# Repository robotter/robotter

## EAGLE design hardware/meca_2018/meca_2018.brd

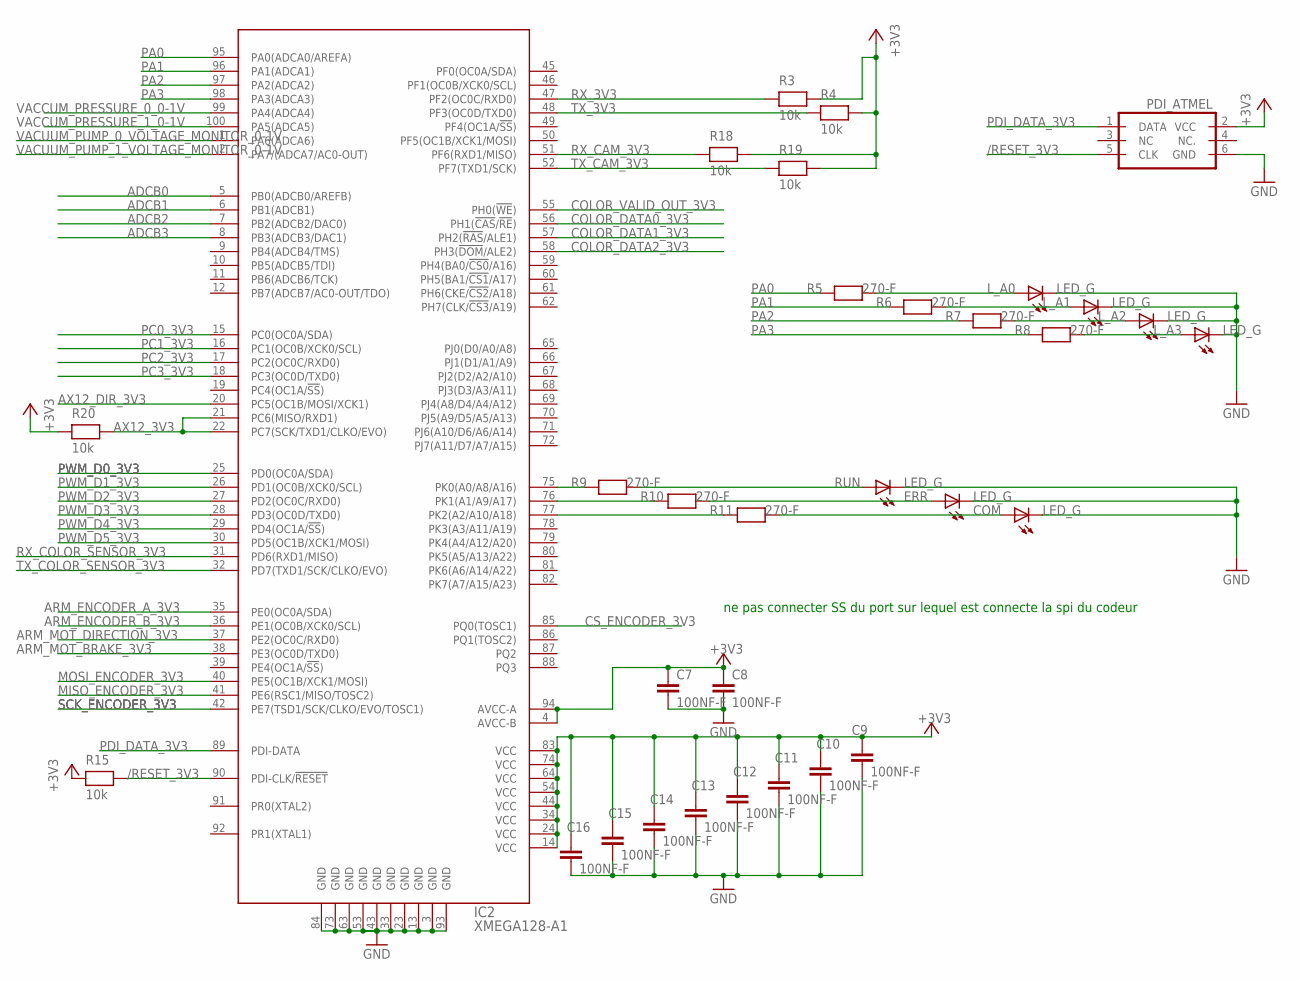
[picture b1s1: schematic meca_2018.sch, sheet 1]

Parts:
C7, C8, C9, C10, C11, C12, C13, C14, C15, C16: 100NF-F; C0603
COM: LED_G; CHIP-LED0805
ERR: LED_G; CHIP-LED0805
IC2: XMEGA128-A1; TQFP100
L_A0, L_A1, L_A2, L_A3: LED_G; CHIP-LED0805
PDI_ATMEL: PDI_ATMEL; ML6
R3, R4, R15, R18, R19, R20: 10k; R0603
R5, R6, R7, R8, R9, R10, R11: 270-F; R0603
RUN: LED_G; CHIP-LED0805

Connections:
+3V3: C7.1, C8.1, C9.1, C10.1, C11.1, C12.1, C13.1, C14.1, C15.1, C16.1, IC2.4 (AVCC-B), IC2.14 (VCC), IC2.24 (VCC), IC2.34 (VCC), IC2.44 (VCC), IC2.54 (VCC), IC2.64 (VCC), IC2.74 (VCC), IC2.83 (VCC), IC2.94 (AVCC-A), PDI_ATMEL.2 (VCC), R3.2, R4.2, R15.1, R18.2, R19.2, R20.1; also elsewhere on the board
/RESET_3V3: IC2.90 (PDI-CLK/!RESET), PDI_ATMEL.5 (CLK), R15.2
ADCB0: IC2.5 (PB0(ADCB0/AREFB))
ADCB1: IC2.6 (PB1(ADCB1))
ADCB2: IC2.7 (PB2(ADCB2/DAC0))
ADCB3: IC2.8 (PB3(ADCB3/DAC1))
ARM_ENCODER_A_3V3: IC2.35 (PE0(OC0A/SDA))
ARM_ENCODER_B_3V3: IC2.36 (PE1(OC0B/XCK0/SCL))
ARM_MOT_BRAKE_3V3: IC2.38 (PE3(OC0D/TXD0))
ARM_MOT_DIRECTION_3V3: IC2.37 (PE2(OC0C/RXD0))
AX12_3V3: IC2.21 (PC6(MISO/RXD1)), IC2.22 (PC7(SCK/TXD1/CLKO/EVO)), R20.2; also elsewhere on the board
AX12_DIR_3V3: IC2.20 (PC5(OC1B/MOSI/XCK1)); also elsewhere on the board
COLOR_DATA0_3V3: IC2.56 (PH1(!CAS!/!RE!))
COLOR_DATA1_3V3: IC2.57 (PH2(!RAS!/ALE1))
COLOR_DATA2_3V3: IC2.58 (PH3(!DOM!/ALE2))
COLOR_VALID_OUT_3V3: IC2.55 (PH0(!WE!))
CS_ENCODER_3V3: IC2.85 (PQ0(TOSC1))
GND: C7.2, C8.2, C9.2, C10.2, C11.2, C12.2, C13.2, C14.2, C15.2, C16.2, COM.C, ERR.C, IC2.3 (GND), IC2.13 (GND), IC2.23 (GND), IC2.33 (GND), IC2.43 (GND), IC2.53 (GND), IC2.63 (GND), IC2.73 (GND), IC2.84 (GND), IC2.93 (GND), L_A0.C, L_A1.C, L_A2.C, L_A3.C, PDI_ATMEL.6 (GND), RUN.C; also elsewhere on the board
MISO_ENCODER_3V3: IC2.41 (PE6(RSC1/MISO/TOSC2)); also elsewhere on the board
MOSI_ENCODER_3V3: IC2.40 (PE5(OC1B/XCK1/MOSI))
unnamed: R9.2, RUN.A
unnamed: ERR.A, R10.2
unnamed: COM.A, R11.2
unnamed: IC2.75 (PK0(A0/A8/A16)), R9.1
unnamed: IC2.76 (PK1(A1/A9/A17)), R10.1
unnamed: IC2.77 (PK2(A2/A10/A18)), R11.1
unnamed: L_A0.A, R5.2
unnamed: L_A1.A, R6.2
unnamed: L_A2.A, R7.2
unnamed: L_A3.A, R8.2
PA0: IC2.95 (PA0(ADCA0/AREFA)), R5.1
PA1: IC2.96 (PA1(ADCA1)), R6.1
PA2: IC2.97 (PA2(ADCA2)), R7.1
PA3: IC2.98 (PA3(ADCA3)), R8.1
PC0_3V3: IC2.15 (PC0(OC0A/SDA))
PC1_3V3: IC2.16 (PC1(OC0B/XCK0/SCL))
PC2_3V3: IC2.17 (PC2(OC0C/RXD0))
PC3_3V3: IC2.18 (PC3(OC0D/TXD0))
PDI_DATA_3V3: IC2.89 (PDI-DATA), PDI_ATMEL.1 (DATA)
PWM_D0_3V3: IC2.25 (PD0(OC0A/SDA)); also elsewhere on the board
PWM_D1_3V3: IC2.26 (PD1(OC0B/XCK0/SCL)); also elsewhere on the board
PWM_D2_3V3: IC2.27 (PD2(OC0C/RXD0)); also elsewhere on the board
PWM_D3_3V3: IC2.28 (PD3(OC0D/TXD0)); also elsewhere on the board
PWM_D4_3V3: IC2.29 (PD4(OC1A/!SS!)); also elsewhere on the board
PWM_D5_3V3: IC2.30 (PD5(OC1B/XCK1/MOSI)); also elsewhere on the board
RX_3V3: IC2.47 (PF2(OC0C/RXD0)), R3.1; also elsewhere on the board
RX_CAM_3V3: IC2.51 (PF6(RXD1/MISO)), R18.1; also elsewhere on the board
RX_COLOR_SENSOR_3V3: IC2.31 (PD6(RXD1/MISO))
SCK_ENCODER_3V3: IC2.42 (PE7(TSD1/SCK/CLKO/EVO/TOSC1))
TX_3V3: IC2.48 (PF3(OC0D/TXD0)), R4.1; also elsewhere on the board
TX_CAM_3V3: IC2.52 (PF7(TXD1/SCK)), R19.1; also elsewhere on the board
TX_COLOR_SENSOR_3V3: IC2.32 (PD7(TXD1/SCK/CLKO/EVO))
VACCUM_PRESSURE_0_0-1V: IC2.99 (PA4(ADCA4))
VACCUM_PRESSURE_1_0-1V: IC2.100 (PA5(ADCA5))
VACUUM_PUMP_0_VOLTAGE_MONITOR_0-1V: IC2.1 (PA6(ADCA6))
VACUUM_PUMP_1_VOLTAGE_MONITOR_0-1V: IC2.2 (PA7/(ADCA7/AC0-OUT))

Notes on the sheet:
ne pas connecter SS du port sur lequel est connecte la spi du codeur

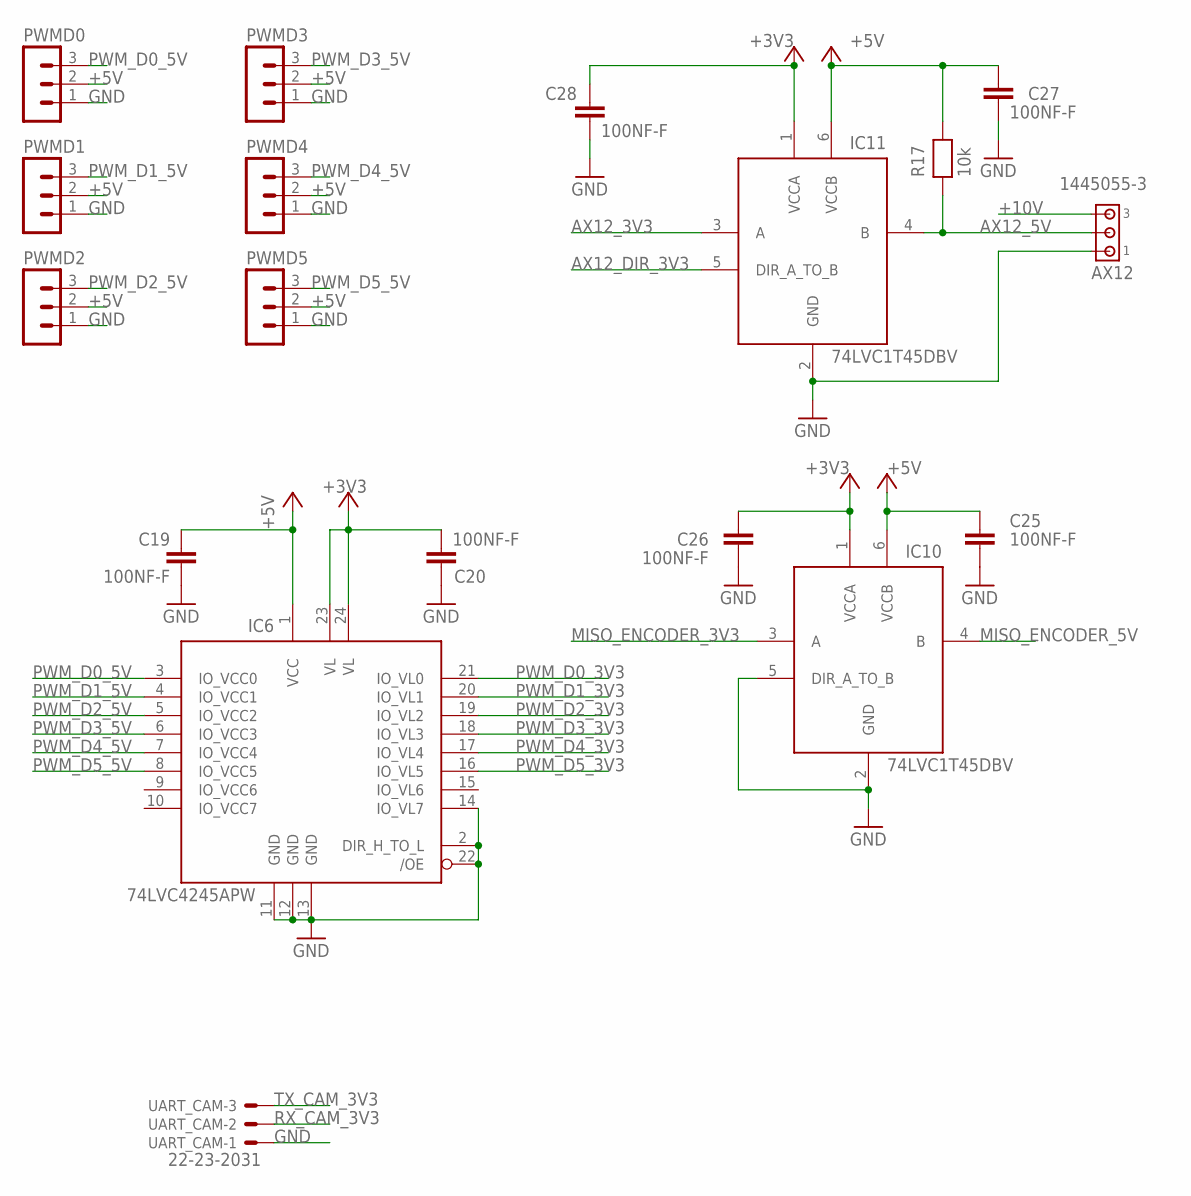
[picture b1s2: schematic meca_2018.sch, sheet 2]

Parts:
AX12: 1445055-3
C19, C20, C25, C26, C27, C28: 100NF-F; C0603
IC6: 74LVC4245APW; TSSOP24
IC10, IC11: 74LVC1T45DBV; SOT23-6
PWMD0, PWMD1, PWMD2, PWMD3, PWMD4, PWMD5: MA03-1
R17: 10k; R0603
UART_CAM: 22-23-2031

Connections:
+3V3: C20.1, C26.1, C28.1, IC6.23 (VL), IC6.24 (VL), IC10.1 (VCCA), IC11.1 (VCCA); also elsewhere on the board
+5V: C19.1, C25.1, C27.1, IC6.1 (VCC), IC10.6 (VCCB), IC11.6 (VCCB), PWMD0.2, PWMD1.2, PWMD2.2, PWMD3.2, PWMD4.2, PWMD5.2, R17.2; also elsewhere on the board
+10V: AX12.3; also elsewhere on the board
AX12_3V3: IC11.3 (A); also elsewhere on the board
AX12_5V: AX12.2, IC11.4 (B), R17.1
AX12_DIR_3V3: IC11.5 (DIR_A_TO_B); also elsewhere on the board
GND: AX12.1, C19.2, C20.2, C25.2, C26.2, C27.2, C28.2, IC6.2 (DIR_H_TO_L), IC6.11 (GND), IC6.12 (GND), IC6.13 (GND), IC6.14 (IO_VL7), IC6.22 (/OE), IC10.2 (GND), IC10.5 (DIR_A_TO_B), IC11.2 (GND), PWMD0.1, PWMD1.1, PWMD2.1, PWMD3.1, PWMD4.1, PWMD5.1, UART_CAM.1; also elsewhere on the board
MISO_ENCODER_3V3: IC10.3 (A); also elsewhere on the board
MISO_ENCODER_5V: IC10.4 (B)
PWM_D0_3V3: IC6.21 (IO_VL0); also elsewhere on the board
PWM_D0_5V: IC6.3 (IO_VCC0), PWMD0.3
PWM_D1_3V3: IC6.20 (IO_VL1); also elsewhere on the board
PWM_D1_5V: IC6.4 (IO_VCC1), PWMD1.3
PWM_D2_3V3: IC6.19 (IO_VL2); also elsewhere on the board
PWM_D2_5V: IC6.5 (IO_VCC2), PWMD2.3
PWM_D3_3V3: IC6.18 (IO_VL3); also elsewhere on the board
PWM_D3_5V: IC6.6 (IO_VCC3), PWMD3.3
PWM_D4_3V3: IC6.17 (IO_VL4); also elsewhere on the board
PWM_D4_5V: IC6.7 (IO_VCC4), PWMD4.3
PWM_D5_3V3: IC6.16 (IO_VL5); also elsewhere on the board
PWM_D5_5V: IC6.8 (IO_VCC5), PWMD5.3
RX_CAM_3V3: UART_CAM.2; also elsewhere on the board
TX_CAM_3V3: UART_CAM.3; also elsewhere on the board

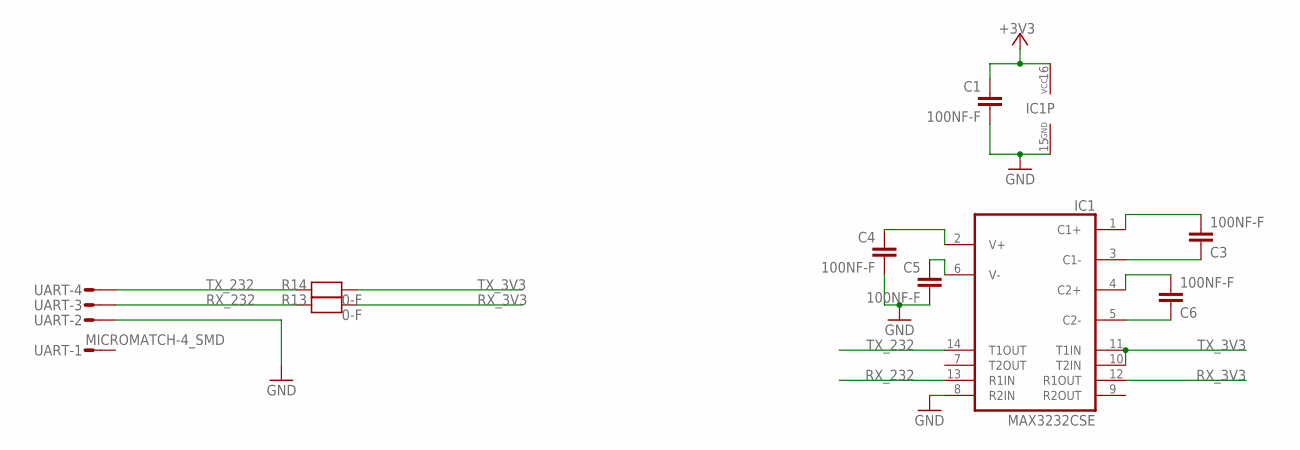
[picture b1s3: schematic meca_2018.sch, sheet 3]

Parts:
C1, C3, C4, C5, C6: 100NF-F; C0603
IC1: MAX3232CSE; SO16
R13, R14: 0-F; R0603
UART: MICROMATCH-4_SMD

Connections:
+3V3: C1.1, IC1.16 (VCC); also elsewhere on the board
GND: C1.2, C4.2, C5.2, IC1.8 (R2IN), IC1.15 (GND), UART.2; also elsewhere on the board
unnamed: C3.1, IC1.1 (C1+)
unnamed: C3.2, IC1.3 (C1-)
unnamed: C6.1, IC1.4 (C2+)
unnamed: C4.1, IC1.2 (V+)
unnamed: C5.1, IC1.6 (V-)
unnamed: C6.2, IC1.5 (C2-)
RX_3V3: IC1.12 (R1OUT), R13.2; also elsewhere on the board
RX_232: IC1.13 (R1IN), R13.1, UART.3
TX_3V3: IC1.10 (T2IN), IC1.11 (T1IN), R14.2; also elsewhere on the board
TX_232: IC1.14 (T1OUT), R14.1, UART.4

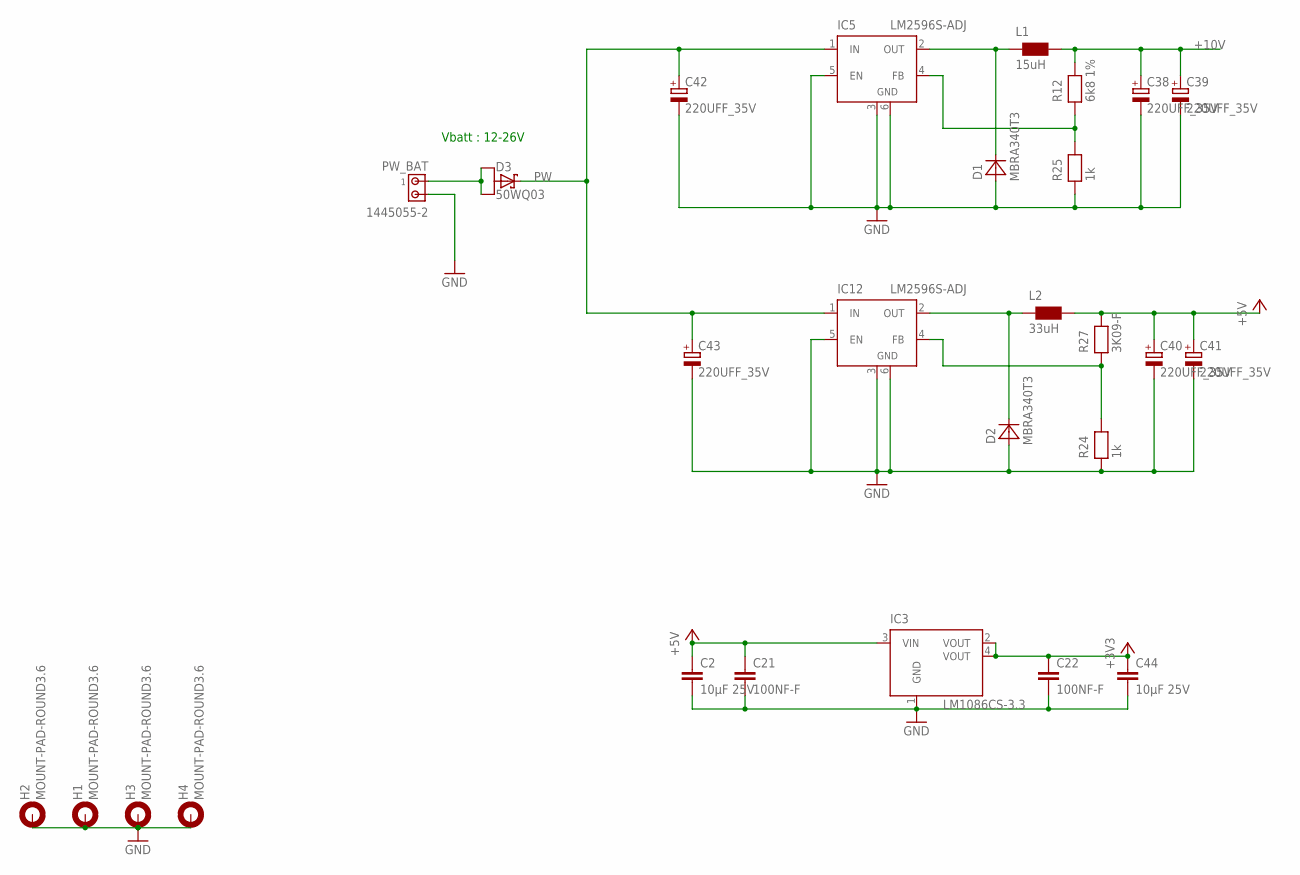
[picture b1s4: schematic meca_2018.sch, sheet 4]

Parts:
C2, C44: 10µF 25V; C1210
C21, C22: 100NF-F; C0603
C38, C39, C40, C41, C42, C43: 220UFF_35V; PANASONIC_F
D1, D2: MBRA340T3; SMA
D3: 50WQ03; TO252
H1, H2, H3, H4: MOUNT-PAD-ROUND3.6; 3,6-PAD
IC3: LM1086CS-3.3; TO263
IC5, IC12: LM2596S-ADJ; TO263-5
L1: 15uH; SRR1280
L2: 33uH; SRR1280
PW_BAT: 1445055-2
R12: 6k8 1%; R0603
R24, R25: 1k; R0603
R27: 3K09-F; R0603

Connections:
+3V3: C22.1, C44.1, IC3.2 (VOUT), IC3.4 (VOUT); also elsewhere on the board
+5V: C2.1, C21.1, C40.+, C41.+, IC3.3 (VIN), L2.2, R27.2; also elsewhere on the board
+10V: C38.+, C39.+, L1.2, R12.2; also elsewhere on the board
GND: C2.2, C21.2, C22.2, C38.-, C39.-, C40.-, C41.-, C42.-, C43.-, C44.2, D1.A, D2.A, H1.B3,6, H2.B3,6, H3.B3,6, H4.B3,6, IC3.1 (GND), IC5.3 (GND), IC5.5 (EN), IC5.6 (GND), IC12.3 (GND), IC12.5 (EN), IC12.6 (GND), PW_BAT.2, R24.1, R25.1; also elsewhere on the board
unnamed: IC12.4 (FB), R24.2, R27.1
unnamed: IC5.4 (FB), R12.1, R25.2
unnamed: D3.1 (A1), D3.3 (A2), PW_BAT.1
unnamed: D1.C, IC5.2 (OUT), L1.1
unnamed: D2.C, IC12.2 (OUT), L2.1
PW: C42.+, C43.+, D3.4 (C), IC5.1 (IN), IC12.1 (IN)

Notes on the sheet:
Vbatt : 12-26V

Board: 2 copper layers, 86 parts (12 on the bottom side), 54 nets, no tracks yet.

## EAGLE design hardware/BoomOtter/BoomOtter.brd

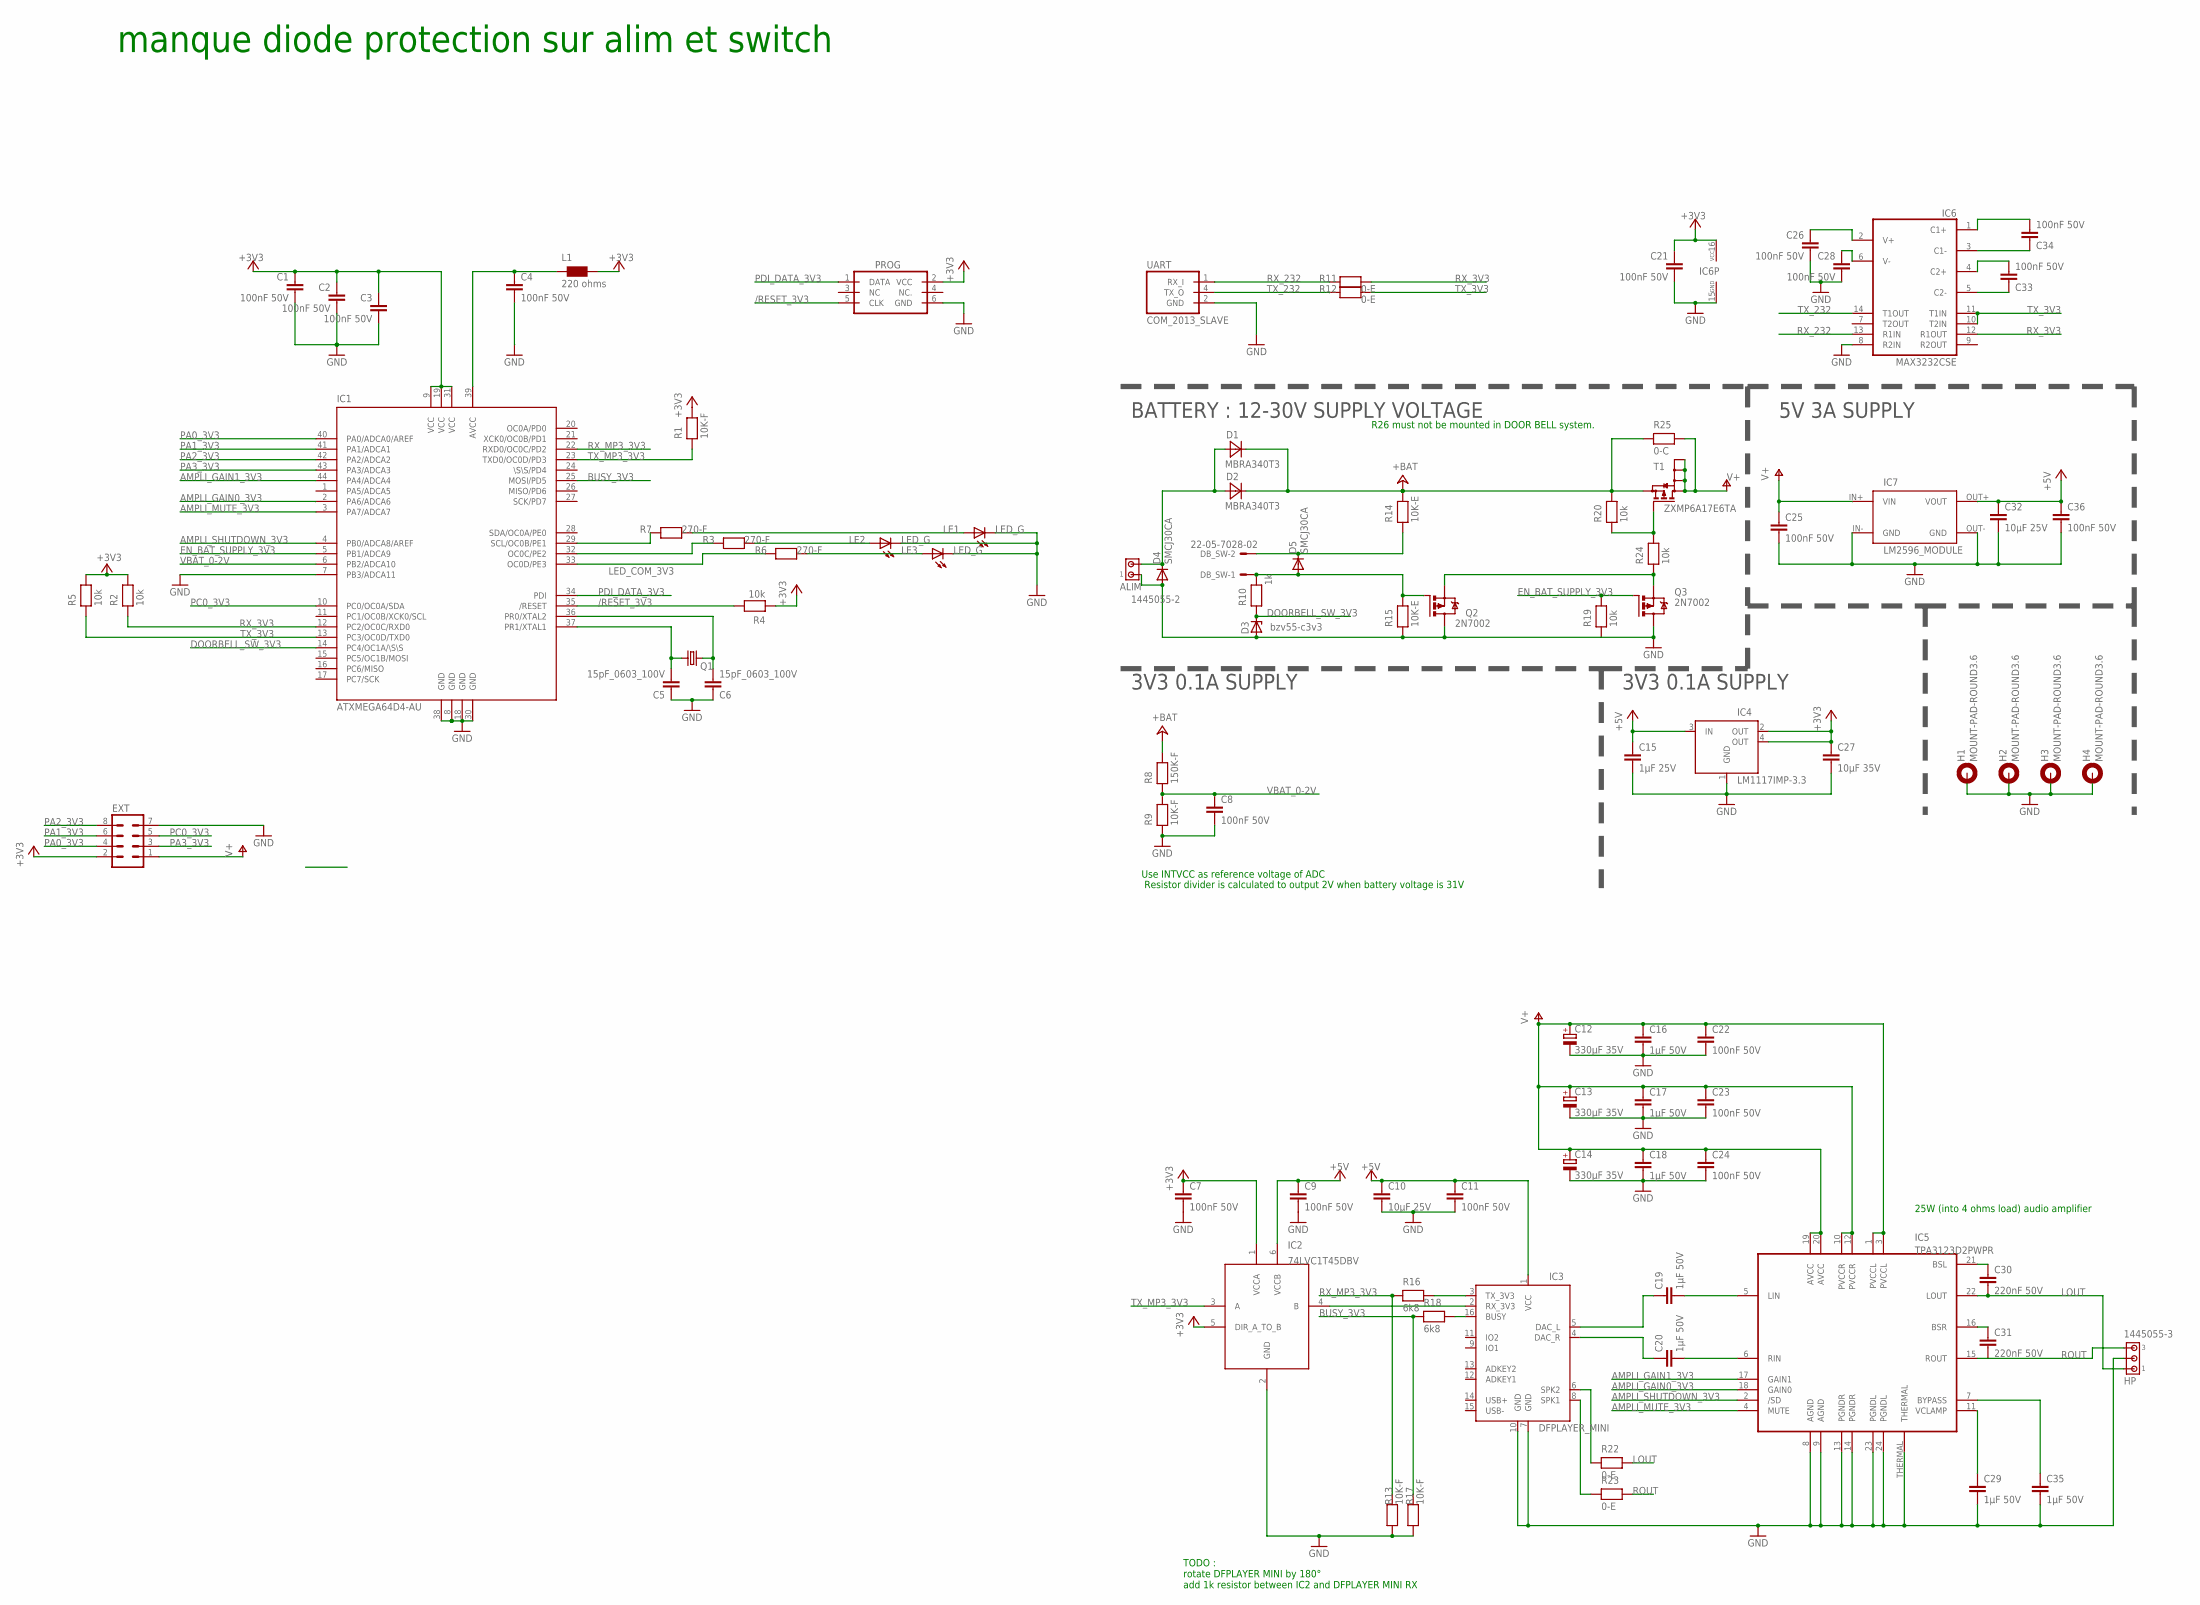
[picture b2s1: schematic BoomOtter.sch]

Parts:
ALIM: 1445055-2
C1, C2, C3, C4, C7, C9, C11, C21, C22, C23, C24, C26, C28, C33, C34, C36: 100nF 50V; C0603
C5, C6: 15pF_0603_100V; C0603
C8, C25: 100nF 50V; C0805
C10, C32: 10µF 25V; C1210
C12, C13, C14: 330µF 35V; PANASONIC_G
C15: 1µF 25V; C1206
C16, C17, C18, C19, C20, C29, C35: 1µF 50V; C1206
C27: 10µF 35V; C1210
C30, C31: 220nF 50V; C0805
D1, D2: MBRA340T3; SMA
D3: bzv55-c3v3; SOD80C
D4, D5: SMCJ30CA; SMC
DB_SW: 22-05-7028-02; 7395-02
EXT: MA04-2
H1, H2, H3, H4: MOUNT-PAD-ROUND3.6; 3,6-PAD
HP: 1445055-3
IC1: ATXMEGA64D4-AU; TQFP44
IC2: 74LVC1T45DBV; SOT23-6
IC3: DFPLAYER_MINI
IC4: LM1117IMP-3.3; SOT223
IC5: TPA3123D2PWPR; HTSSOP24
IC6: MAX3232CSE; SO16
IC7: LM2596_MODULE; LM2596
L1: 220 ohms; R0603
LE1, LE2, LE3: LED_G; CHIP-LED0805
PROG: PDI_ATMELL; ML6L
Q1: CRYSTAL_16MHZ_5032; CRYSTAL_5032
Q2, Q3: 2N7002; SOT23
R1, R9, R13, R17: 10K-F; R0603
R2, R4, R5, R19, R20, R24: 10k; R0603
R3, R6, R7: 270-F; R0603
R8: 150K-F; R0603
R10: 1k; R0603
R11, R12, R22, R23: 0-E; R0805
R14, R15: 10K-E; R0805
R16, R18: 6k8; R0603
R25: 0-C; R1210
T1: ZXMP6A17E6TA; SOT26
UART: COM_2013_SLAVE; MICROMATCH-4_SMD

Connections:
+3V3: C1.1, C2.1, C3.1, C7.1, C21.1, C27.1, EXT.2, IC1.9 (VCC), IC1.19 (VCC), IC1.31 (VCC), IC2.1 (VCCA), IC2.5 (DIR_A_TO_B), IC4.2 (OUT), IC4.4 (OUT), IC6.16 (VCC), L1.2, PROG.2 (VCC), R1.2, R2.2, R4.1, R5.2
+5V: C9.1, C10.1, C11.1, C15.1, C32.1, C36.1, IC2.6 (VCCB), IC3.1 (VCC), IC4.3 (IN), IC7.OUT+ (VOUT)
+BAT: D1.C, D2.C, R8.2, R14.2, R20.2, R25.1, T1.4 (S)
/RESET_3V3: IC1.35 (/RESET), PROG.5 (CLK), R4.2
AMPLI_GAIN0_3V3: IC1.2 (PA6/ADCA6), IC5.18 (GAIN0)
AMPLI_GAIN1_3V3: IC1.44 (PA4/ADCA4), IC5.17 (GAIN1)
AMPLI_MUTE_3V3: IC1.3 (PA7/ADCA7), IC5.4 (MUTE)
AMPLI_SHUTDOWN_3V3: IC1.4 (PB0/ADCA8/AREF), IC5.2 (/SD)
BUSY_3V3: IC1.25 (MOSI/PD5), R17.2, R18.1
DOORBELL_SW_3V3: D3.C, IC1.14 (PC4/OC1A/\S\S), R10.1
EN_BAT_SUPPLY_3V3: IC1.5 (PB1/ADCA9), Q3.1 (G), R19.2
GND: ALIM.1, C1.2, C2.2, C3.2, C4.2, C5.1, C6.1, C7.2, C8.2, C9.2, C10.2, C11.2, C12.-, C13.-, C14.-, C15.2, C16.2, C17.2, C18.2, C21.2, C22.2, C23.2, C24.2, C25.2, C26.2, C27.2, C28.2, C29.2, C32.2, C35.2, C36.2, D3.A, D4.A, EXT.7, H1.B3,6, H2.B3,6, H3.B3,6, H4.B3,6, HP.2, IC1.7 (PB3/ADCA11), IC1.8 (GND), IC1.18 (GND), IC1.30 (GND), IC1.38 (GND), IC2.2 (GND), IC3.7 (GND), IC3.10 (GND), IC4.1 (GND), IC5.8 (AGND), IC5.9 (AGND), IC5.13 (PGNDR), IC5.14 (PGNDR), IC5.23 (PGNDL), IC5.24 (PGNDL), IC5.THERMAL, IC6.8 (R2IN), IC6.15 (GND), IC7.IN- (GND), IC7.OUT- (GND), LE1.C, LE2.C, LE3.C, PROG.6 (GND), Q2.2 (D), Q3.2 (D), R9.1, R13.1, R15.1, R17.1, R19.1, UART.2 (GND)
LED_COM_3V3: IC1.29 (SCL/OC0B/PE1), R7.1
LOUT: C30.2, HP.1, IC5.22 (LOUT), R22.2
unnamed: C34.1, IC6.1 (C1+)
unnamed: LE2.A, R3.2
unnamed: ALIM.2, D1.A, D2.A, D4.C
unnamed: LE3.A, R6.2
unnamed: C34.2, IC6.3 (C1-)
unnamed: C33.1, IC6.4 (C2+)
unnamed: LE1.A, R7.2
unnamed: Q2.3 (S), Q3.3 (S), R24.1
unnamed: IC1.32 (OC0C/PE2), R3.1
unnamed: IC1.33 (OC0D/PE3), R6.1
unnamed: C26.1, IC6.2 (V+)
unnamed: C19.1, IC3.5 (DAC_L)
unnamed: C28.1, IC6.6 (V-)
unnamed: C6.2, IC1.36 (PR0/XTAL2), Q1.2
unnamed: D5.C, DB_SW.2, R14.1
unnamed: C4.1, IC1.39 (AVCC), L1.1
unnamed: D5.A, DB_SW.1, Q2.1 (G), R10.2, R15.2
unnamed: C20.1, IC3.4 (DAC_R)
unnamed: C20.2, IC5.6 (RIN)
unnamed: C19.2, IC5.5 (LIN)
unnamed: C30.1, IC5.21 (BSL)
unnamed: IC3.3 (TX_3V3), R16.2
unnamed: C33.2, IC6.5 (C2-)
unnamed: C31.1, IC5.16 (BSR)
unnamed: C35.1, IC5.7 (BYPASS)
unnamed: IC3.6 (SPK2), R22.1
unnamed: IC3.8 (SPK1), R23.1
unnamed: IC3.16 (BUSY), R18.2
unnamed: IC2.4 (B), IC3.2 (RX_3V3)
unnamed: C5.2, IC1.37 (PR1/XTAL1), Q1.1
unnamed: R20.1, R24.2, T1.3 (G)
PA0_3V3: EXT.4, IC1.40 (PA0/ADCA0/AREF)
PA1_3V3: EXT.6, IC1.41 (PA1/ADCA1)
PA2_3V3: EXT.8, IC1.42 (PA2/ADCA2)
PA3_3V3: EXT.3, IC1.43 (PA3/ADCA3)
PC0_3V3: EXT.5, IC1.10 (PC0/OC0A/SDA)
PDI_DATA_3V3: IC1.34 (PDI), PROG.1 (DATA)
ROUT: C31.2, HP.3, IC5.15 (ROUT), R23.2
RX_3V3: IC1.12 (PC2/OC0C/RXD0), IC6.12 (R1OUT), R2.1, R11.2
RX_232: IC6.13 (R1IN), R11.1, UART.1 (RX_I)
RX_MP3_3V3: IC1.22 (RXD0/OC0C/PD2), R13.2, R16.1
TX_3V3: IC1.13 (PC3/OC0D/TXD0), IC6.10 (T2IN), IC6.11 (T1IN), R5.1, R12.2
TX_232: IC6.14 (T1OUT), R12.1, UART.4 (TX_O)
TX_MP3_3V3: IC1.23 (TXD0/OC0D/PD3), IC2.3 (A), R1.1
V+: C12.+, C13.+, C14.+, C16.1, C17.1, C18.1, C22.1, C23.1, C24.1, C25.1, EXT.1, IC5.1 (PVCCL), IC5.3 (PVCCL), IC5.10 (PVCCR), IC5.12 (PVCCR), IC5.19 (AVCC), IC5.20 (AVCC), IC7.IN+ (VIN), R25.2, T1.1 (D), T1.2 (D), T1.5 (D), T1.6 (D)
VBAT_0-2V: C8.1, IC1.6 (PB2/ADCA10), R8.1, R9.2
VCLAMP: C29.1, IC5.11 (VCLAMP)

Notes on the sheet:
BATTERY : 12-30V SUPPLY VOLTAGE
Use INTVCC as reference voltage of ADC
Resistor divider is calculated to output 2V when battery voltage is 31V
5V 3A SUPPLY
R26 must not be mounted in DOOR BELL system.
manque diode protection sur alim et switch
3V3 0.1A SUPPLY
25W (into 4 ohms load) audio amplifier
TODO : rotate DFPLAYER MINI by 180° add 1k resistor between IC2 and DFPLAYER MINI RX

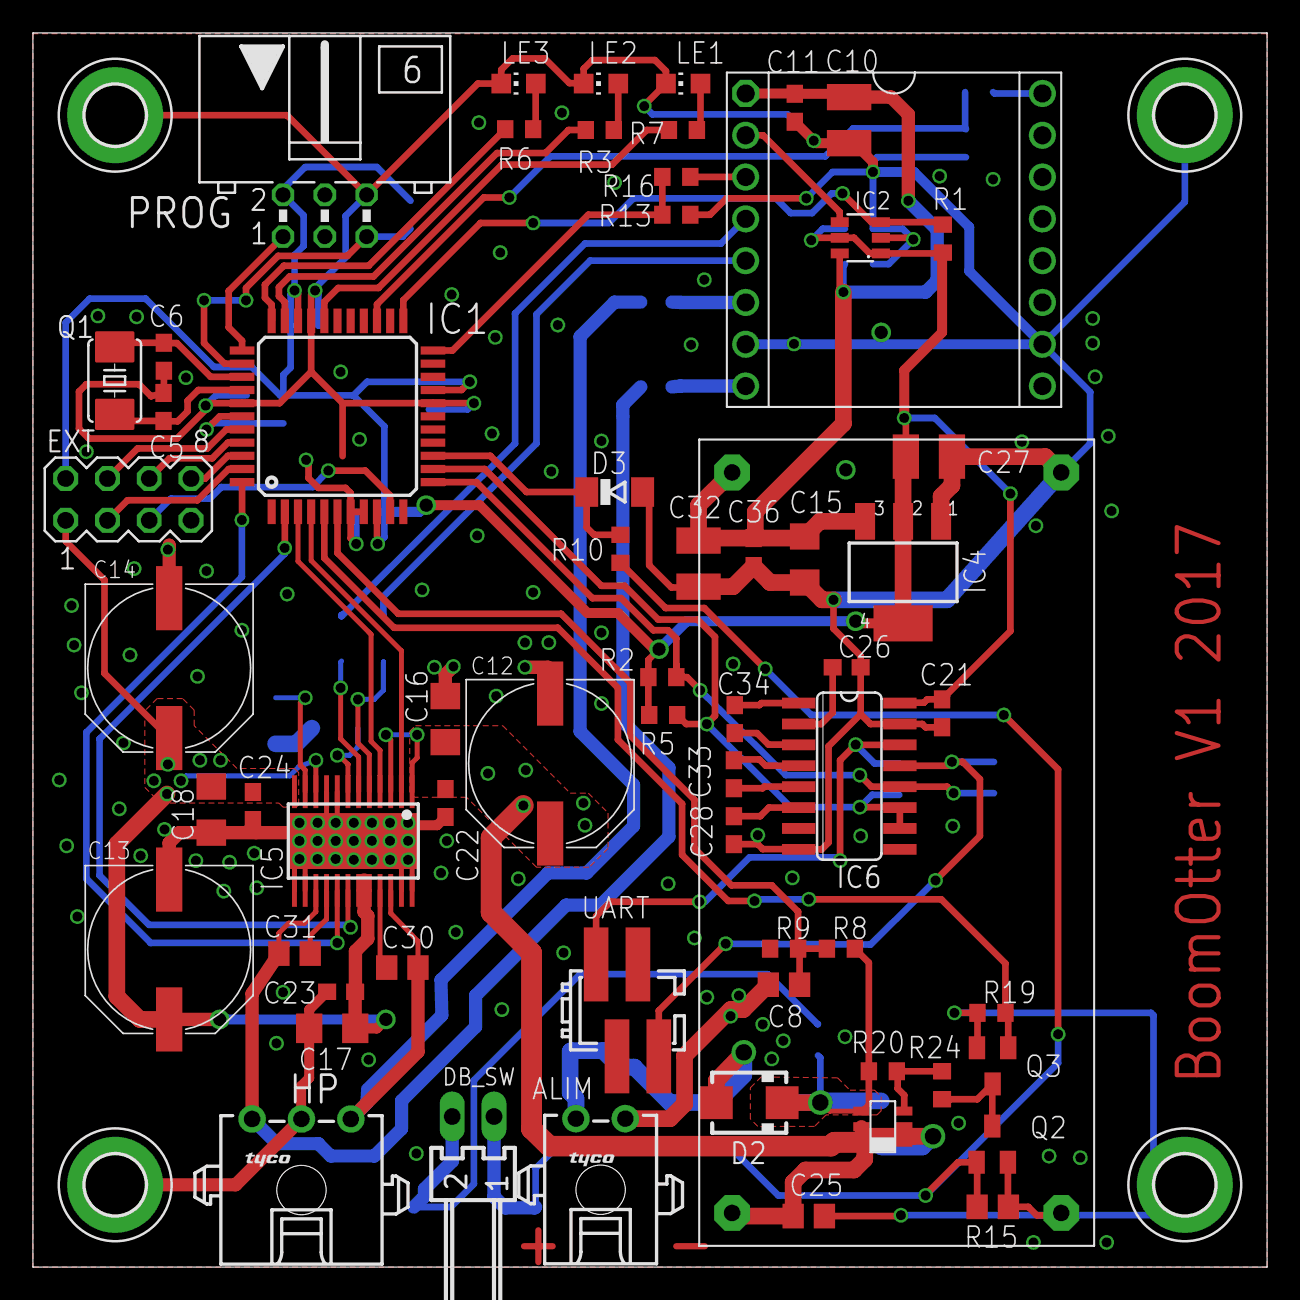
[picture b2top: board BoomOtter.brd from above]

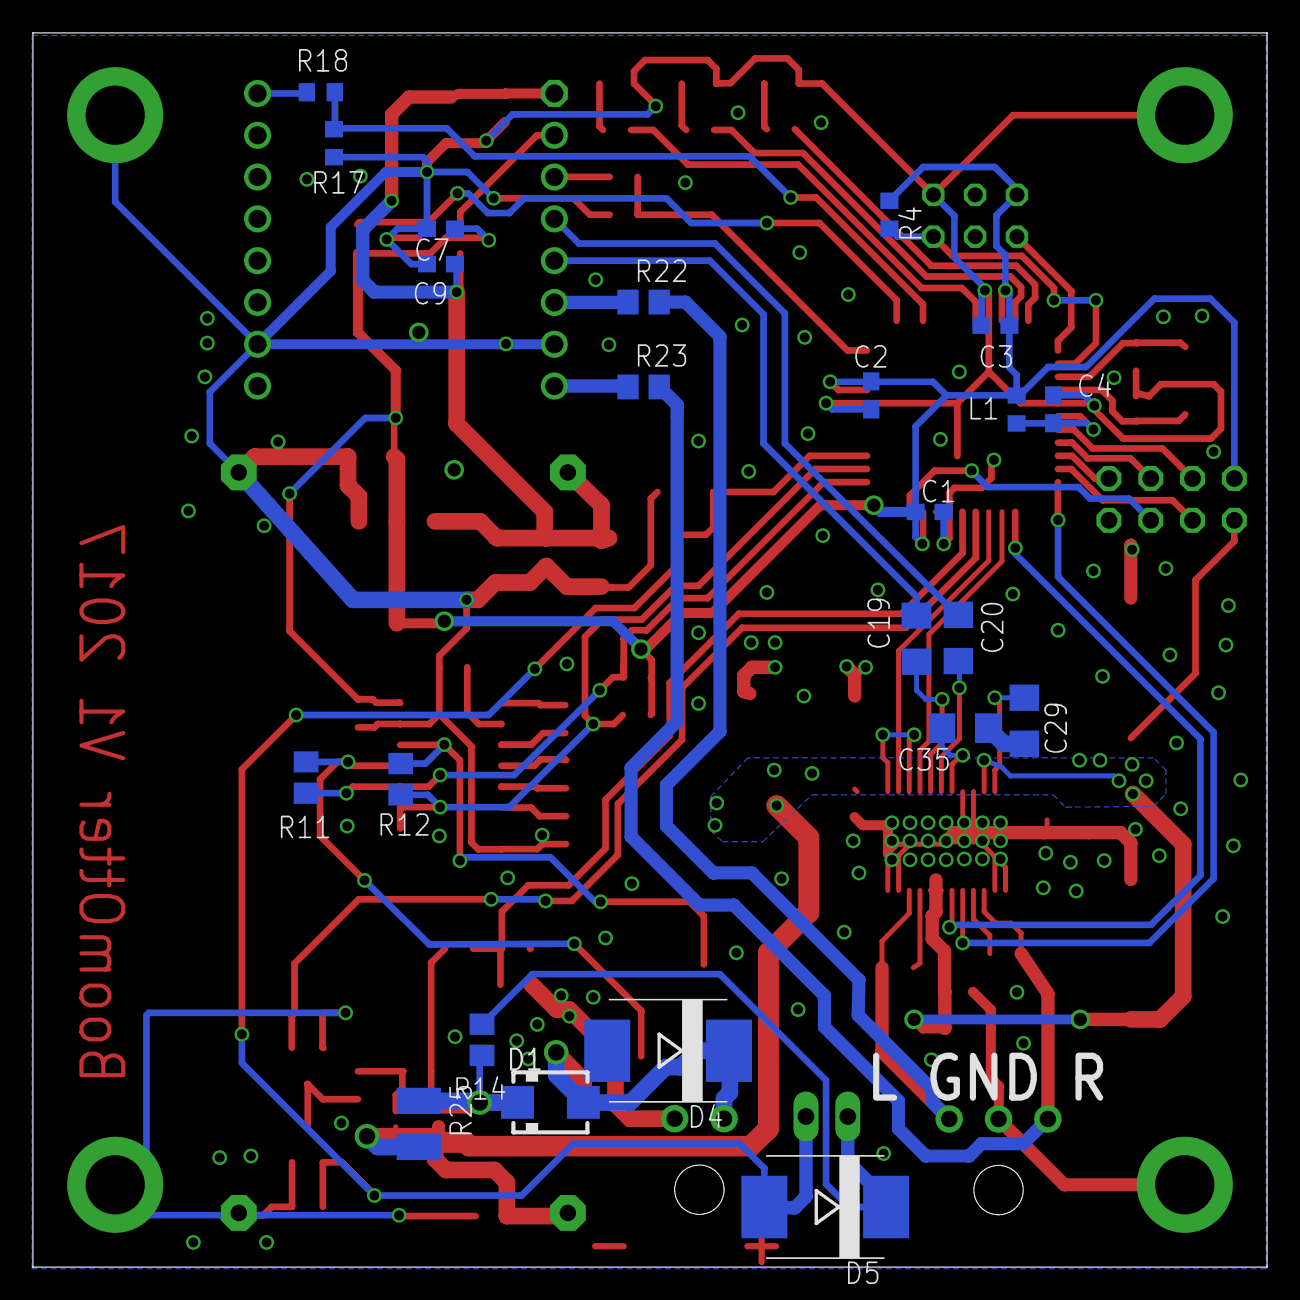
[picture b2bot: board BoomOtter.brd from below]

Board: 2 copper layers, 75.0 x 75.0 mm, 90 parts (23 on the bottom side), 61 nets.
